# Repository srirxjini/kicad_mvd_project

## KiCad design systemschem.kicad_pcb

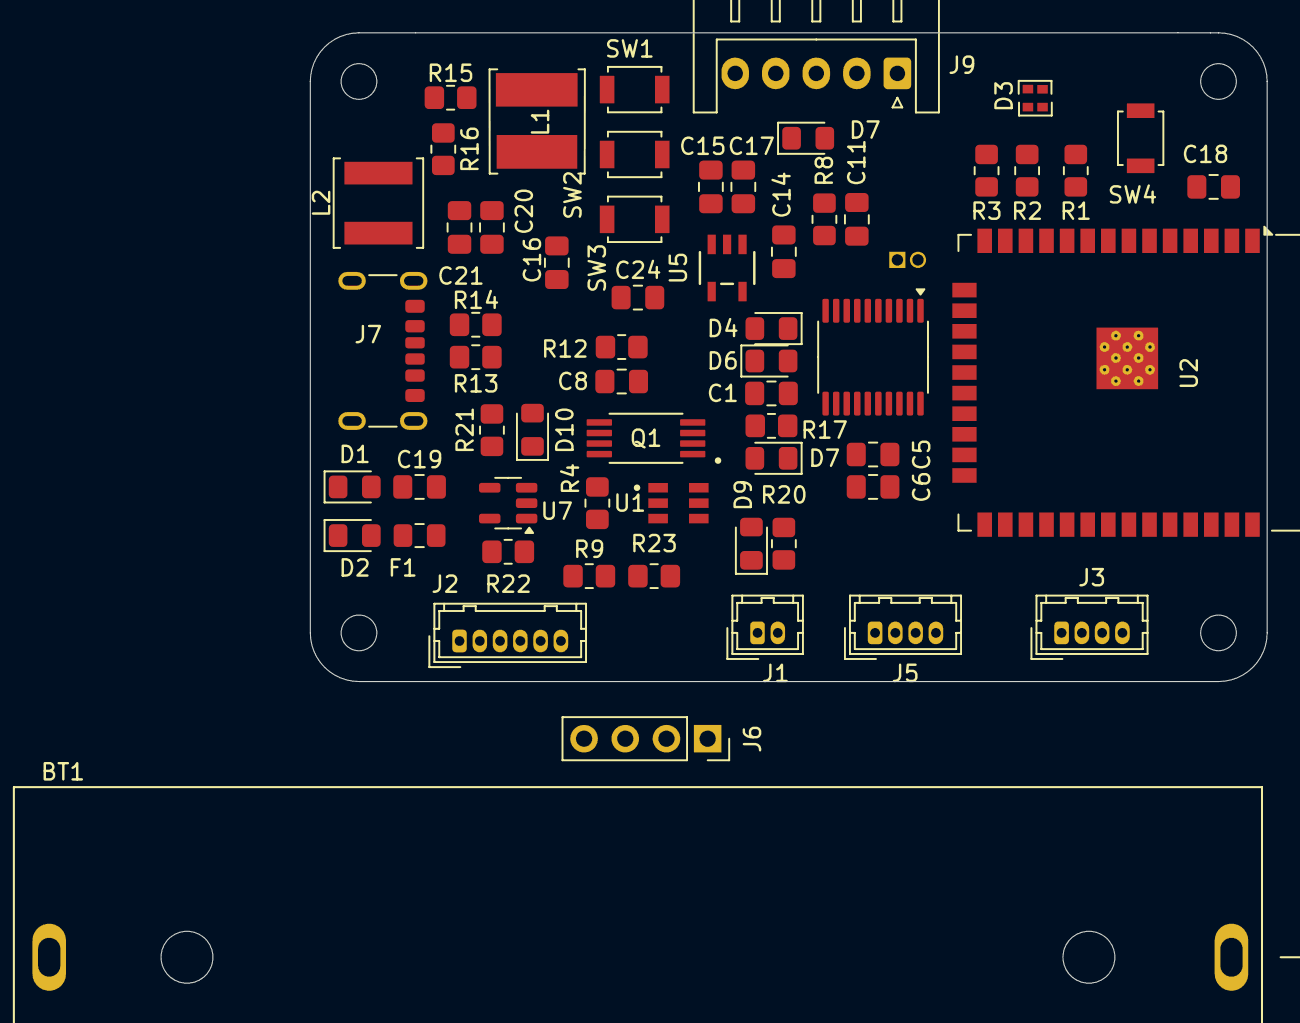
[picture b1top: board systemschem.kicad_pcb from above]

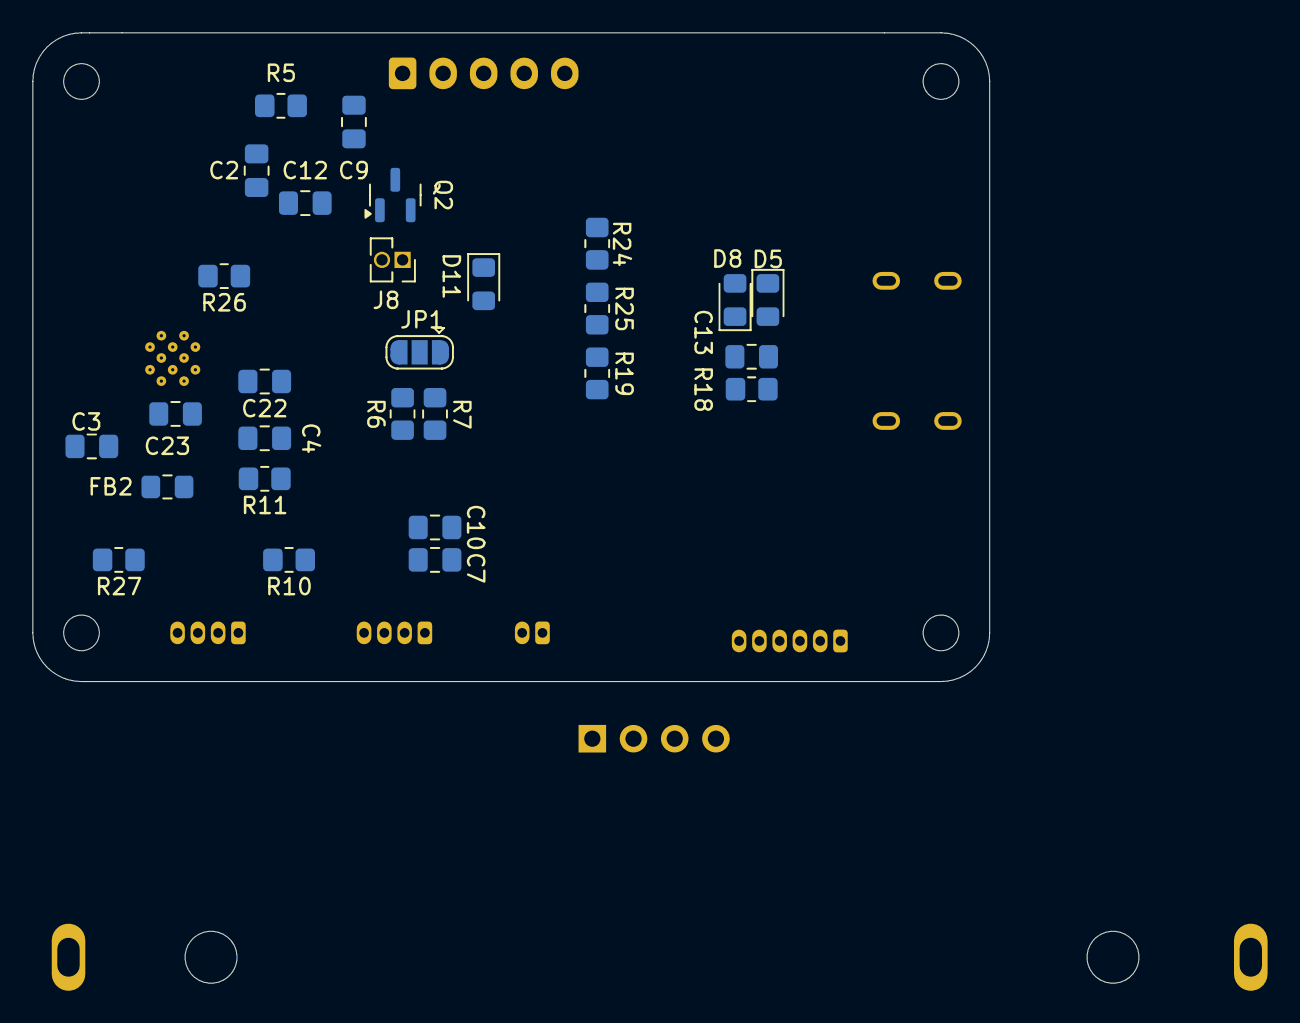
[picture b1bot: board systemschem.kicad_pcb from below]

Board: 2 copper layers, 59.0 x 40.0 mm, 92 parts (28 on the bottom side), 54 nets, no tracks yet.

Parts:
BT1: BK-18650-PC2; BAT_BK-18650-PC2
C1, C2, C13, C21, C23, C24: 10u; C_0805_2012Metric_Pad1.18x1.45mm_HandSolder
C3, C6, C18: 1u; C_0805_2012Metric_Pad1.18x1.45mm_HandSolder
C4, C8, C9, C12, C20, C22: 0.1u; C_0805_2012Metric_Pad1.18x1.45mm_HandSolder
C5: 10n; C_0805_2012Metric_Pad1.18x1.45mm_HandSolder
C7, C11: 100n; C_0805_2012Metric_Pad1.18x1.45mm_HandSolder
C10: 4.7u; C_0805_2012Metric_Pad1.18x1.45mm_HandSolder
C14: 22pF; C_0805_2012Metric_Pad1.18x1.45mm_HandSolder
C15, C17: 22uF; C_0805_2012Metric_Pad1.18x1.45mm_HandSolder
C16: 22u; C_0805_2012Metric_Pad1.18x1.45mm_HandSolder
C19: 2.2u; C_0805_2012Metric_Pad1.18x1.45mm_HandSolder
D1, D7, D11: D_Schottky_Dual_CommonAnode_AKK_Split; D_0805_2012Metric_Pad1.15x1.40mm_HandSolder
D2, D6, D8: D_TVS; D_0805_2012Metric_Pad1.15x1.40mm_HandSolder
D3: LED_AGBR; LED_Cree-PLCC4_3.2x2.8mm_CCW
D4, D5, D9: BZT52Bxx; D_0805_2012Metric_Pad1.15x1.40mm_HandSolder
D7#2: 1N4148; D_0805_2012Metric_Pad1.15x1.40mm_HandSolder
D10: Red; LED_0805_2012Metric_Pad1.15x1.40mm_HandSolder
F1: Fuse; Fuse_0805_2012Metric_Pad1.15x1.40mm_HandSolder
FB2: FerriteBead; L_0805_2012Metric_Pad1.15x1.40mm_HandSolder
H1, H2, H3, H4: MountingHole; MountingHole_2.2mm_M2
J1: Conn_01x02; Hirose_DF13-02P-1.25DSA_1x02_P1.25mm_Vertical
J2: Conn_01x06; Hirose_DF13-06P-1.25DSA_1x06_P1.25mm_Vertical
J3, J5: Conn_01x04; Hirose_DF13-04P-1.25DSA_1x04_P1.25mm_Vertical
J6: Conn_01x04_Pin; PinSocket_1x04_P2.54mm_Vertical
J7: USB_C_Receptacle_PowerOnly_6P; USB_C_Receptacle_GCT_USB4125-xx-x_6P_TopMnt_Horizontal
J8: BZ1; PinSocket_1x02_P1.27mm_Vertical
J9: Conn_01x05; JST_XH_S5B-XH-A_1x05_P2.50mm_Horizontal
JP1: SolderJumper_3_Open; SolderJumper-3_P1.3mm_Open_RoundedPad1.0x1.5mm
L1, L2: 2.2uH; L_Sunlord_SWPA5040S
Q1: FS8205A; SOP65P640X120-8N
Q2: NMOS; SOT-23
R1, R2: 150; R_0805_2012Metric_Pad1.20x1.40mm_HandSolder
R3: 220; R_0805_2012Metric_Pad1.20x1.40mm_HandSolder
R4, R6, R7: 1k; R_0805_2012Metric_Pad1.20x1.40mm_HandSolder
R5, R8, R9, R13, R14, R19, R23, R24, R25, R27: 10k; R_0805_2012Metric_Pad1.20x1.40mm_HandSolder
R10, R11, R12, R17, R18, R20, R26: 100; R_0805_2012Metric_Pad1.20x1.40mm_HandSolder
R15: 200k; R_0805_2012Metric_Pad1.20x1.40mm_HandSolder
R16: 100k; R_0805_2012Metric_Pad1.20x1.40mm_HandSolder
R21: 330; R_0805_2012Metric_Pad1.20x1.40mm_HandSolder
R22: 2.2k; R_0805_2012Metric_Pad1.20x1.40mm_HandSolder
SW1, SW2, SW3, SW4: SW_Push; SW_SPST_B3U-1000P
U1: DW01A; SOT95P280X145-6N
U2: ESP32-WROOM-32D
U3: STM32F030F4Px; TSSOP-20_4.4x6.5mm_P0.65mm
U5: SY8089AAAC; SY8089AAAC_SGY-M
U7: LTC4054ES5-4.2; TSOT-23-5

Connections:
+3.3V: C2.1, C3.1, C4.1, C5.2, C6.2, C7.1, C9.1, C10.1, C18.1, C21.1, C22.1, D3.1 (A), D7#2.1 (K), D11.2 (K), FB2.1, J5.4, J6.1, J8.2, J9.5, L2.2, R5.1, R6.1, R8.1, R9.1, R19.1, R23.2, R24.1, R25.1, U2.2 (VDD), U3.5 (VDDA), U3.16 (VDD), U5.1 (EN)
+5V: C19.2, D1.1 (A), F1.2, J7.A9 (VBUS), J7.B9 (VBUS), R21.1, U7.4 (V_{CC})
B+: BT1.+, C16.2, C24.2, R12.2, U5.4 (IN), U7.3 (BAT)
B-: BT1.-, C1.2, C2.2, C3.2, C4.2, C5.1, C6.1, C7.2, C8.2, C9.2, C10.2, C11.2, C12.1, C13.1, C15.1, C16.1, C17.1, C18.2, C19.1, C20.2, C21.2, C24.1, D2.1 (A1), D4.2 (A), D5.2 (A), D6.1 (A1), D8.1 (A1), D9.2 (A), D10.1 (K), J1.2, J3.4, J5.3, J6.4, J7.A12 (GND), J7.B12 (GND), J7.S1 (SHIELD), J9.2, J9.3, Q1.2, Q1.3, Q2.3 (S), R7.2, R13.1, R14.1, R16.2, R22.2, R27.2, SW1.2, SW2.2, SW3.1, SW4.1, U1.6 (GND), U2.1 (GND), U2.15 (GND), U2.38 (GND), U2.39 (GND), U3.15 (VSS), U5.2 (GND), U7.1 (~CHRG), U7.2 (GND)
Bat Voltage: R20.2, U3.10 (PA4)
Buzzer: R26.2, U2.8 (IO32)
Current: R18.2, U3.12 (PA6)
EN: C12.2, R5.2, SW4.2, U2.3 (EN)
LED_Blue: R1.1, U2.10 (IO25)
LED_Green: R2.1, U2.11 (IO26)
LED_Red: R3.1, U2.12 (IO27)
unnamed: C14.2, C15.2, C17.2, C20.1, L1.2, L2.1, R15.1
unnamed: C22.2, C23.2
unnamed: D1.2 (K), D2.2 (A2), F1.1
unnamed: D3.3 (BK), R1.2
unnamed: D3.2 (GK), R2.2
unnamed: D3.4 (RK), R3.2
unnamed: C1.1, D4.1 (K), D6.2 (A2), J9.1, R17.2
unnamed: C13.2, D5.1 (K), D8.2 (A2), J9.4, R18.1
unnamed: D7.2 (K), R17.1
unnamed: D9.1 (K), J1.1, R20.1
unnamed: D10.2 (A), R21.2
unnamed: D11.1 (A), J8.1, Q2.1 (D)
unnamed: C23.1, FB2.2, J3.1
unnamed: J3.2, R10.1
unnamed: J3.3, R11.1
unnamed: J7.A5 (CC1), R14.2
unnamed: J7.B5 (CC2), R13.2
unnamed: JP1.1 (A), R7.1
unnamed: JP1.3 (B), R6.2
unnamed: JP1.2 (C), U3.1 (BOOT0)
unnamed: Q1.6, Q1.7, R4.2
unnamed: Q2.2 (G), R26.1
unnamed: R4.1, U1.2 (CS)
unnamed: Q1.5, U1.3 (OC)
unnamed: Q1.4, U1.1 (OD)
unnamed: C8.1, R12.1, U1.5 (VCC)
unnamed: R27.1, U2.25 (IO0)
unnamed: C11.1, R8.2, U3.4 (NRST)
unnamed: C14.1, R15.2, R16.1, U5.5 (FB)
unnamed: L1.1, U5.3 (LX)
unnamed: R22.1, U7.5 (PROG)
RXN1: U2.26 (IO4), U3.18 (PA10)
RXN2: R11.2, U2.28 (IO17)
SCL: J6.2, R23.1, U2.13 (IO14)
SDA: J6.3, R9.2, U2.14 (IO12)
SWDCLK: J5.2, U3.20 (PA14)
SWDIO: J5.1, U3.19 (PA13)
TXN1: U2.29 (IO5), U3.17 (PA9)
TXN2: R10.2, U2.27 (IO16)
Voltage: D7.1 (A), U3.11 (PA5)
sw1: R24.2, SW1.1, U2.37 (IO23)
sw2: R25.2, SW2.1, U2.9 (IO33)
sw3: R19.2, SW3.2, U2.6 (IO34)
